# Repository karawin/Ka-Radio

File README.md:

# ** ESP8266 & VS1053 Wifi WebRadio ** #

### Ka-Radio, a WiFi shoutcast player based on ESP8266 and VS1053b chips</br>
See also the esp32 version at https://github.com/karawin/Ka-Radio32</br>

## Basic informations<BR/>
### New
A new android application is born
  
- KaRadio Remote Control by Vassilis Serasidis on google Play.

It is an easy and fast WiFi remote control for your KaRadio or KaRadio32 hardware.  
With this android app you can select the WebRadio station you want to play, set the volume and get the station information such as Station name, Genre, Bit rate, Meta data and more.   
Found it at
https://play.google.com/store/apps/details?id=com.serasidis.karadio.rc

Thanks Vassilis.  
###  
### Release 1.9 R8 - Built on 2021/01/01

#### Add On: add a lcd, a remote control, and other goodies: see https://github.com/karawin/Karadio-addons 

#### Attention:
The optional led is now on GPIO2. The blue led on the ESP8266 is blinking at the same rate.  
GPIO16 is now the Chip select for the external ram if any.<BR/>
The external ram is detected at boot time if present.    
To load this release, please flash   
boot_v1.6.bin at 0x0000,  
user1.4096.new.4.bin at 0x1000 ,  
user2.4096.new.4.bin at 0X81000,  
esp_init_data_default.bin at 0x3FC000   
and blank.bin at	0x3fe000   
After that, all next updates are done with the On The Air (OTA) feature.  
<BR/>  
See also https://hackaday.io/project/11570-wifi-webradio-with-esp8266-and-vs1053   

#### Loading the esp8266
The binaries are on ESP8266-Firmware/bin/upgrade/

#### First use
- If the access point of your router is not known, the webradio inits itself as an AP. Connect the wifi of your computer to the ssid "WifiWebRadio",  
- Browse to 192.168.4.1 to display the page, got to "setting" "Wifi" and configure your ssid ap, the password if any, the wanted IP or use dhcp if you know how to retrieve the dhcp given ip (terminal or scan of the network).
- In the gateway field, enter the ip address of your router.
- Validate. The equipment restart to the new configuration. Connect your wifi to your AP and browse to the ip given in configuration.
- Congratulation, you can edit your own station list. Dont forget to save your stations list in case of problem or for new equipments.
- if the AP is already know by the esp8266, the default ip is given by dhcp.
- a sample of stations list is on https://github.com/karawin/Ka-Radio/blob/master/ESP8266-Firmware/WebStations.txt . Can be uploaded via the web page.   
- Karadio can be controlled by the web interface or by the uart interface or by telnet. List of commands: type help  
- See the list of command at http://karadio.karawin.fr/Interface.txt  

### Generate Ka-Radio
see the http://karadio.karawin.fr/readme.txt file.

### History:
- Based on https://github.com/PiotrSperka/ESP8266-WebRadio<br />
- New development based on the new https://github.com/espressif/ESP8266_RTOS_SDK<br />
- Compiled with [esp-open-sdk](https://github.com/pfalcon/esp-open-sdk)<br />
- Compatible with mobile<br />
- Stable<br />
- tools to save and restore the stations database<br /><br />
- prototype made with:<br />
-- http://fr.aliexpress.com/item/MB102-Breadboard-Power-Supply-Module-3-3V-5V-For-Solderless-Breadboard/2027279953.html (0.74 euros)<br />
-- http://www.ebay.fr/itm/121775761053?_trksid=p2057872.m2749.l2649&ssPageName=STRK%3AMEBIDX%3AIT  (3,09 euros)<br />
-- http://www.ebay.fr/itm/401046111343?_trksid=p2060353.m2749.l2649&ssPageName=STRK%3AMEBIDX%3AIT  (6 euros)<br />
-- http://www.ebay.fr/itm/131683794035?_trksid=p2060353.m2749.l2649&ssPageName=STRK%3AMEBIDX%3AIT  (1.05 euros)<br />
-- http://fr.aliexpress.com/item/USB-to-TTL-converter-UART-module-CH340G-CH340-3-3V-5V-switch/32392228218.html?detailNewVersion=2 (0.59 euro)<br />
-- some wires ...<br /><br />
- Wiring: <br />
From ESP8266_ESP12( 3.3 v) to VS1053 (5 v)<br />
REST<br />
ADC   if control panel is not used, this input must be grounded.<br />
CH_PD to 3.3v<br />
GPIO16 (a 1Hz output)<br />
GPIO14 to VS1053 SCK<br />
GPIO12 to VS1053 MISO<br />
GPIO13 to VS1053 MOSI<br />
<br />
TXD to   CH340G UART rx<br />
RXD from CH340G UART tx<br />
GPIO05 to VS1053 XDCS<br />
GPIO04 to VS1053 DREQ<br />
GPIO00 to VS1053 XRST<br />
GPIO02<br />
GPIO15 to VS1053 XCS<br />
<br/>
Optional external ram (23LCV1024) support (1:CS/=GPIO16 2:MISO=GPIO12 3:NC 4:GND 5:MOSI=GPIO13 6:SCK=GPIO14 7:GND 8:3.3v)<br/>
If your chip has a /Vhold in place of /VBAT, the pin 7 must be wired to VCC (pin8)<br/>
Attention:<br>
	The optional led is now on GPIO2. The blue led on the ESP8266 is blinking at the same rate.<br/>
	GPIO16 is now the Chip select for the external ram if any.<br/>
	The external ram is detected at boot time if present.<br/>

## Used hardware
WiFi : ESP8266 (ESP-12 with 32Mbits flash)<br />
Additional MCU (as a bridge UART<=>UI): AVR<br />
Audio decoder: VS1053<br />

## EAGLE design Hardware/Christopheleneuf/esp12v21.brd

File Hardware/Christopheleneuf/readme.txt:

These eagle files are from christopheleneuf.

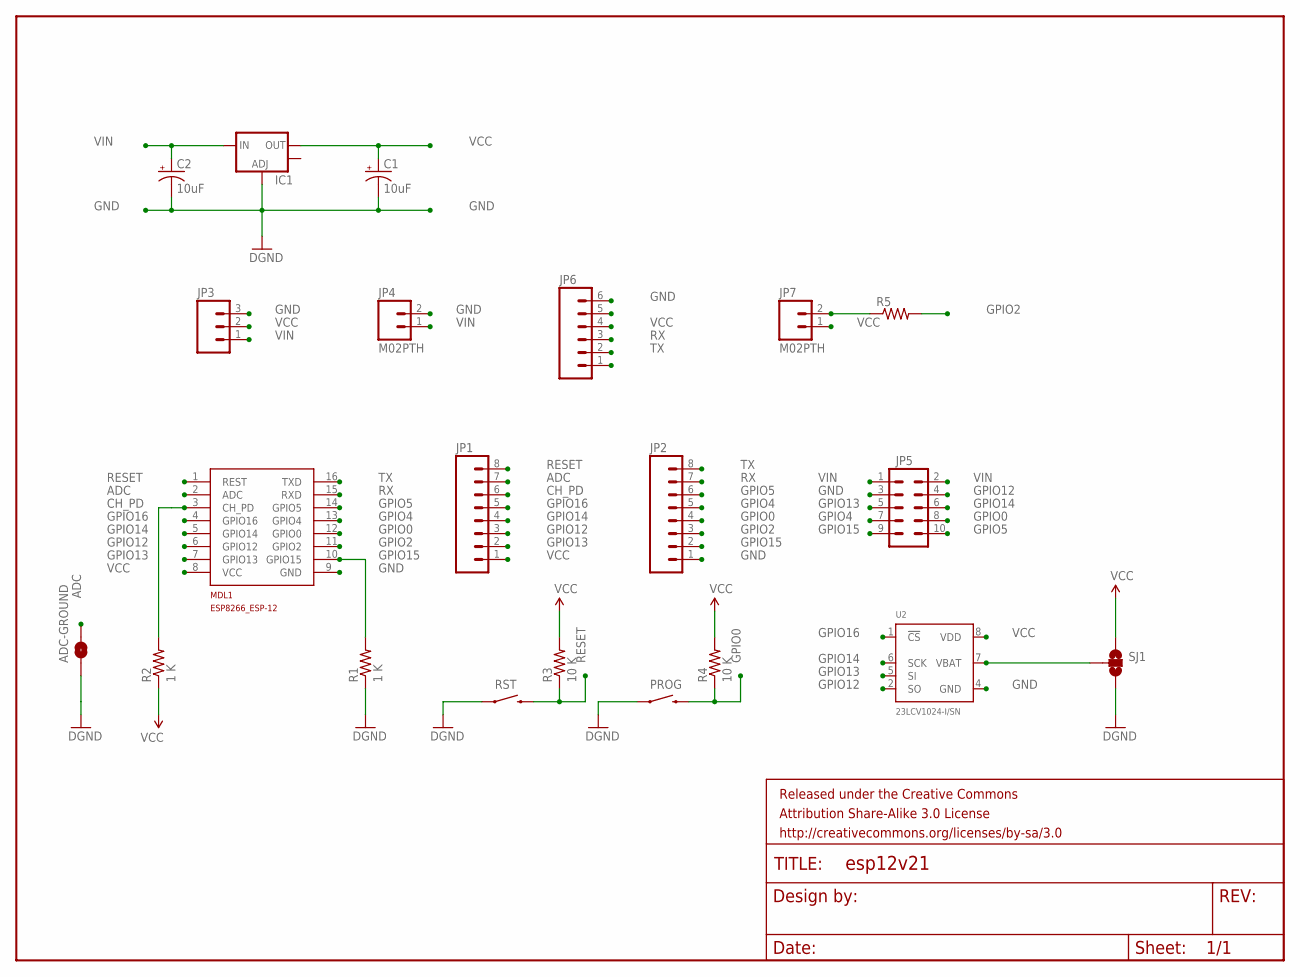
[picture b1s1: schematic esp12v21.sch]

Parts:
ADC-GROUND: SOLDERJUMPERNO; SJ_2S-NO
C1, C2: 10uF; EIA3216
FRAME1: FRAME-LETTER; CREATIVE_COMMONS
IC1: V_REG_LM1117SOT223; SOT223
JP1, JP2: M081X08; 1X08
JP3: M03PTH; 1X03
JP4, JP7: M02PTH; 1X02
JP5: M05X2NO_SILK; 2X5_NOSILK
JP6: M06LOCK; 1X06_LOCK
MDL1: ESP8266-12GPIO04/05_CORRECTED; ESP8266-ESP12
PROG: SWITCH-MOMENTARY-2-SMD-1101NE; TACTILE-SWITCH-1101NE
R1, R2: 1 K; 0805
R3, R4: 10 K; 0805
R5: RESISTOR0805-RES; 0805
RST: SWITCH-MOMENTARY-2-SMD-1101NE; TACTILE-SWITCH-1101NE
SJ1: SOLDERJUMPER_2WAYS; SJ_3
U2: 23LCV1024-I/SN; SO8

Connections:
ADC: ADC-GROUND.2, JP1.7, MDL1.2 (ADC)
CH_PD: JP1.6, MDL1.3 (CH_PD), R2.2
GND: ADC-GROUND.1, C1.C (-), C2.C (-), IC1.1 (ADJ), JP2.1, JP3.3, JP4.2, JP5.3, JP6.6, MDL1.9 (GND), PROG.P$1 (1), R1.1, RST.P$1 (1), SJ1.3, U2.4 (GND)
GPIO0: JP2.4, JP5.8, MDL1.12 (GPIO0), PROG.P$2 (2), R4.1
GPIO2: JP2.3, MDL1.11 (GPIO2), R5.2
GPIO4: JP2.5, JP5.7, MDL1.13 (GPIO4)
GPIO5: JP2.6, JP5.10, MDL1.14 (GPIO5)
GPIO12: JP1.3, JP5.4, MDL1.6 (GPIO12), U2.2 (SO)
GPIO13: JP1.2, JP5.5, MDL1.7 (GPIO13), U2.5 (SI)
GPIO14: JP1.4, JP5.6, MDL1.5 (GPIO14), U2.6 (SCK)
GPIO15: JP2.2, JP5.9, MDL1.10 (GPIO15), R1.2
GPIO16: JP1.5, MDL1.4 (GPIO16), U2.1 (!CS)
unnamed: SJ1.2, U2.7 (VBAT)
unnamed: JP7.2, R5.1
RESET: JP1.8, MDL1.1 (REST), R3.1, RST.P$2 (2)
RX: JP2.7, JP6.3, MDL1.15 (RXD)
TX: JP2.8, JP6.2, MDL1.16 (TXD)
VCC: C1.A (+), IC1.2 (OUT), JP1.1, JP3.2, JP6.4, JP7.1, MDL1.8 (VCC), R2.1, R3.2, R4.2, SJ1.1, U2.8 (VDD)
VIN: C2.A (+), IC1.3 (IN), JP3.1, JP4.1, JP5.1, JP5.2

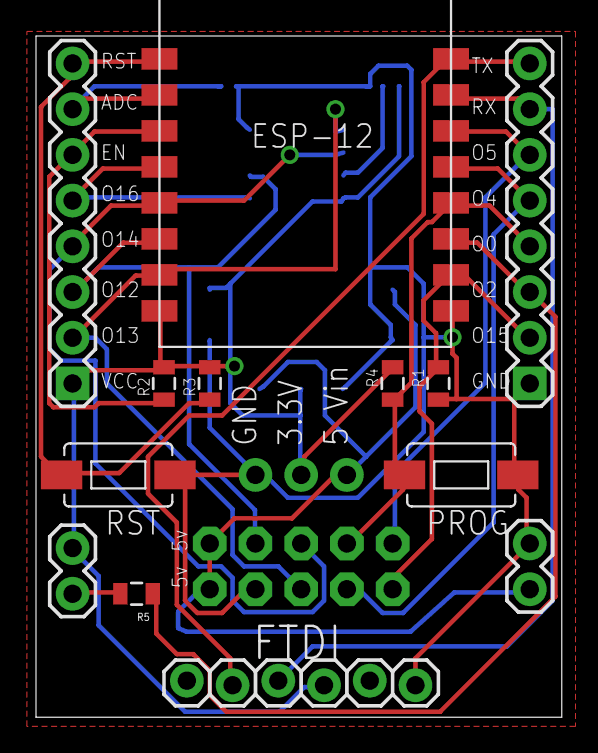
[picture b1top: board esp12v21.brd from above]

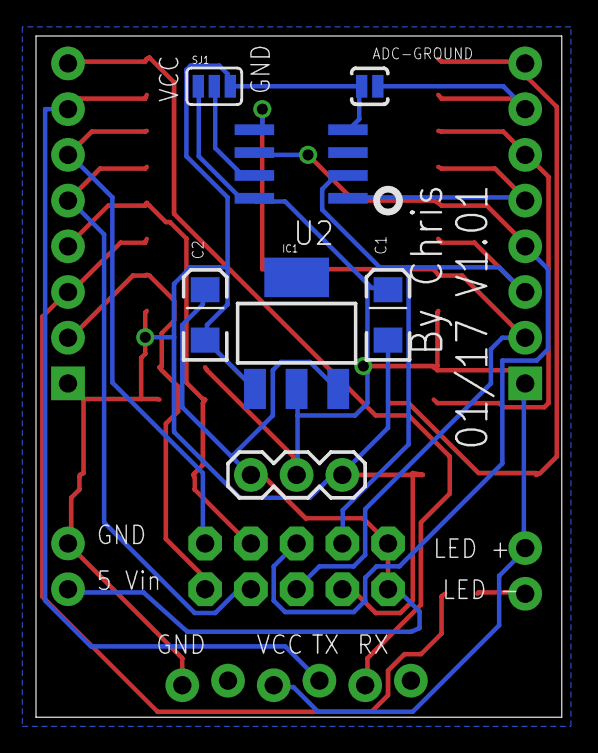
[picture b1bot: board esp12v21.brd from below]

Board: 2 copper layers, 29.2 x 37.8 mm, 22 parts (7 on the bottom side), 19 nets.

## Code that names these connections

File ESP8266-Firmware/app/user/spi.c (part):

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		PIN_FUNC_SELECT(PERIPHS_IO_MUX_SD_DATA1_U, 1);	
	}else if(spi_no==HSPI){
		WRITE_PERI_REG(PERIPHS_IO_MUX, 0x105|(clock_div_flag<<9)); //Set bit 9 if 80MHz sysclock required
		PIN_FUNC_SELECT(PERIPHS_IO_MUX_MTDI_U, 2); //GPIO12 is HSPI MISO pin (Master Data In)
		PIN_FUNC_SELECT(PERIPHS_IO_MUX_MTCK_U, 2); //GPIO13 is HSPI MOSI pin (Master Data Out)
		PIN_FUNC_SELECT(PERIPHS_IO_MUX_MTMS_U, 2); //GPIO14 is HSPI CLK pin (Clock)
		//PIN_FUNC_SELECT(PERIPHS_IO_MUX_MTDO_U, 2); //GPIO15 is HSPI CS pin (Chip Select / Slave Select)
	}

}
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
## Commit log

2016-06-15 New repository
2016-06-16 Correction for NodeMcu with adc dividor and grounded adc.
2016-06-16 New start
2016-06-16 removed some traces
2016-06-18 piotSperka merged this release.
2016-06-26 Release 1.0.5
2016-06-27 Increase stack size a bit...
2016-06-27 Readme
2016-07-19 Release 1.0.6
2016-07-21 External ram detection
    External ram detection
    and Save stations from webradio changed for edge
2016-07-21 History in upgrade
2016-07-29 Increase spi clock for external ram
2016-07-29 Increas spi clock for external ram
    restore spi speed before flash read/write
2016-08-01 receive buffer too big
2016-08-14 Release 1.0.7
2016-09-12 Release 1.0.8
2016-09-12 Release 1.0.8. Readme
2016-09-14 A little bug in metadata
2016-09-15 cleanup
2016-09-16 IF a station is not found, indicate it to the interface in the name.
2016-09-17 A little crash removed...
2016-09-29 Release 1.0.9
2016-09-29 Release 1.0.9 Md file
2016-10-01 I2S mistake corrected
2016-10-10 Release 1.0.10
2016-10-10 1.0.10 Led blink too quickly for my taste.
2016-10-16 release 1.1.0
2016-10-16 Readme 1.1.0
2016-10-29 Release 1.1.1
2016-10-29 Release 1.1.1 ReadMe
2016-11-09 karadioU8glib.zip added: lcd software
    karadioU8glib.zip is an arduino sketch to build a lcd display for
    karadio.
    Some many other little improvments in karadion.
    No new features added.
2016-11-23 1.1.2
2016-11-26 1.1.2 stable
2016-11-26 controle.pdf updated
2016-12-01 Release 1.1.3
2016-12-03 lcd & remote arduino software
2017-01-02 Cleanup 1.1.3
2017-01-08 pre 1.1.4
2017-01-09 1.1.4
2017-01-09 ReadMe 1.1.4
2017-01-10 1.1.4 links in readme
2017-01-14 1.1.5
2017-01-14 1.1.5 readme.md
2017-01-20 mistake default ip
2017-01-24 lcd update
2017-01-25 1.1.5, AP mode corrected
2017-01-31 Wire external ram
2017-02-02 Release 1.1.6
2017-02-02 1.1.6 Read.me
2017-02-09 1.1.7
2017-02-09 Readme 1.1.7
2017-02-10 1.1.7+
    volume offset correction
2017-02-12 Fixed the bug with reduced size of payload buffer. TCP package data size checked with tcpdump. It is 1024 bytes now. Faster loading of webpage.
2017-02-12 servfile update
2017-03-30 Fix syntax errors.
2017-03-30 Fix syntax errors (test)
2017-04-04 Release 1.1.8
2017-04-04 1.1.8 correction
2017-04-04 Readme 1.1.8
2017-04-13 Release 1.2
2017-04-13 Readme 1.2
2017-04-14 Priority uart
2017-04-18 README.md formatting changes
2017-04-20 restore index.html
2017-05-02 Added some missing include and cleaned the Makefile
2017-05-02 Update readme for yui_compressor
2017-05-07 added the readme.txt
2017-05-07 Added readme.txt to generate Ka-Radio
2017-05-08 KaRadio-install.sh added
2017-05-16 Minor details for the volume
2017-05-22 Release 1.2.2
2017-05-30 Release 1.3
2017-06-01 Readme update
2017-06-06 Rlease 1.3.1
2017-06-19 Release 1.3.2
2017-06-19 1.3.2
2017-06-30 Release 1.3.3
    Bugs removed
2017-07-01 interface.txt update
2017-07-04 Control panel on bar ESP
2017-07-11 1.3.4
2017-07-19 Release 1.4
    July, 19 2017
2017-07-19 patch comment inverted.
2017-07-24 Release 1.5
    New KaraDio based on Espressif RTOS SDK 1.5.0-dev
2017-07-25 1.5 update
2017-07-29 1.4.1 released
    Back to 1.4 line
2017-07-30 Cleaning things
2017-07-31 Revision 4
2017-07-31 Some labels changed.
2017-08-01 1.4.2
2017-08-01 1.4.2 R3
2017-08-07 Release 1.5
2017-08-08 1.5 R3
2017-08-11 1.5.1 R1
2017-08-12 offset volume negative was wrong
2017-08-25 R 1.6
2017-08-25 R 1.6 json correction
2017-08-27 Ajust uart speed not working. Corrected.
2017-09-05 little change on uart
2017-09-17 Release 1.6.1
2017-10-21 eeprom
2017-11-02 release 1.6.2
2017-11-02 Readme 1.6.2
2017-11-08 1.6.2 R2
2017-11-08 1.6.2 R3
2017-11-22 ntp server changed
2017-11-22 Version 1.6.2 R4
2017-12-27 1.6.3: Correction for stations with the char & in path.
2018-09-05 pre release 1.7
    Web command prev and next added
    mdns in progress.
2018-09-09 pre 1.7 mdns
2018-09-09 Version 1.7 official
    <ul>
    <li>mDns added </li>
    <li>web commands next and prev added</li>
    <li>uart or teknet command sys.host added.</li>
    </ul>
2018-09-09 a wrong label
2018-11-21 Replacing yui compressor with python script
2018-11-27 1.7 R1
    Title on top of the page
2019-01-15 style and readme.md
2019-02-01 Release 1.8 R0
2019-02-01 1.8 volume arrow
2019-02-01 Correction for instant-play
2019-02-06 Release 1.8 R1
2019-02-07 script.js detail
2019-02-11 1.8 R2
2019-02-11 Corrected: Wifi infos, upgrade
2019-02-15 prerelease 1.9 R0
2019-02-21 ESP8266 RTOS SDK 2.0.0
2019-02-25 inteface
2019-02-25 Revert "ESP8266 RTOS SDK 2.0.0"
2019-02-25 Restore ESP8266 RTOS SDK 2.0.0
2019-02-26 Release 1.9 R0 RTOS_SDK 2.0.0
2019-02-27 1.9 R0 final
2019-02-27 1.9 R0 binaries
2019-02-27 README.md
2019-02-28 Disable telnet in AP mode
2019-03-02 Html infos bug
2019-03-07 keyboard on web (ctrl space)
2019-04-08 Release 1.9 R1
2019-04-15 1.9 R2
    AP mode was not working
2019-04-28 Release 1.9 R3
2019-05-18 lwip update. AP corretion if no ip given.
2019-05-26 1.9 R4
    lwip tuning
2019-06-30 Release 1.9 R5
    json correction
2019-08-01 Problem on AP mode due to the lwip layer. Resolved
    Seems resolved
2020-01-11 Release 1.9 R6
2020-12-20 Release 1.9 R7
    new vs1053b patch 2.9
2021-01-01 Release 1.9 R8
    VS1053B Code cleaned
2021-01-09 Release 9
    VS1053b detection improved.
    On some old vs1003/vs1053 boards, loading the vs1053 patch result in no
    sound because the vs1053 board resetted to the midi mode. Corrected now.
    Setting panel correction.
2021-01-09 Bug no patch
2021-01-10 WebStations.txt update
2021-01-28 Release V2.0R0
    Better handling of long header moved playlist
    timezone suggestion
    Better monitoring
2021-02-10 Release V2.1 R0
    No clear password in message for security.
2021-02-14 Release V2.1 R0 new
    <ul id="ordered">
    <li>Security: the ssid passwords are no longer sent
    on each "Setting" display, but only when changed.</li>
    <li>Bug fixed:
    in parse playlist. Possible memory leak. Thanks to HmarikBel</li>
    <li>Bug fixed: Special char in station name was incorrectly sent.</li>
2021-02-15 2.1 R0 Little pb
    New station not saved.
2021-03-12 Release 2.1 R1
    Some mistakes on wifi init
2021-03-12 2.1 R1 forgot one file
2021-03-24 Readme.md update
2022-10-22 Fix for wifi password 2 not saved correctly

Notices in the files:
ESP8266-Firmware/app/user/spi.c:
The MIT License (MIT)
Copyright (c) 2015 David Ogilvy (MetalPhreak)
parts and their libraries:
SparkFun-Connectors: Licensing: CC v3.0 Share-Alike You are welcome to use this library for commercial purposes.
SparkFun-Aesthetics: Released under the Creative Commons Attribution Share-Alike 3.0 License
SparkFun-Aesthetics: http://creativecommons.org/licenses/by-sa/3.0
